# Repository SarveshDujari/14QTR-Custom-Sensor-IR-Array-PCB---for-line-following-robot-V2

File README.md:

# 14-Channel QTR Sensor Array PCB

Custom 14-channel infrared sensor array PCB designed in KiCad for high-speed line follower robots and embedded robotics applications.

---

## Preview

### PCB Layout

### 3D View

---

## Features

- 14× TCRT5000 IR reflectance sensors
- Custom U-shaped curved PCB for wide-angle sensing
- Compact sensor spacing for accurate line detection
- Angled side sensors for better curve and junction detection
- Mounting holes for chassis integration
- Dedicated resistor network for each channel
  - 200Ω IR LED series resistor
  - 10kΩ pull-down resistor
- 16-pin single-row output header
- Analog output for all channels
- Compatible with any ADC-capable microcontroller
- Onboard decoupling capacitor for stable power delivery
- Designed in KiCad 9.0
- Gerber files included for fabrication

---

## Hardware Specifications

| Parameter | Value |
|---|---|
| Sensor Type | TCRT5000 |
| Sensor Count | 14 |
| LED Series Resistor | 200 Ω |
| Pull-down Resistor | 10 kΩ |
| Decoupling Capacitor | 100 nF |
| Supply Voltage | 5V |
| Output Type | Analog |
| Header Type | 16-pin 2.54mm single-row |
| PCB Type | 2-Layer Custom PCB |
| Software Used | KiCad 9.0 |
| Main Application | Line Follower Robotics |

---

## Bill of Materials (BOM)

| Reference | Component | Value | Quantity |
|---|---|---|---|
| U1–U14 | IR Reflectance Sensor | TCRT5000 | 14 |
| R1, R3, R5 ... R27 | LED Series Resistor | 200 Ω (0805) | 14 |
| R2, R4, R6 ... R28 | Pull-down Resistor | 10 kΩ (0805) | 14 |
| C1 | Decoupling Capacitor | 100 nF (0805) | 1 |
| J1 | Pin Header | 16-pin 2.54mm | 1 |
| — | Power Connector | Header / Screw Terminal | 1 |

---

## Pinout

| Pin | Signal | Description |
|---|---|---|
| 1 | GND | Ground |
| 2 | VIN | 5V Supply |
| 3–16 | CH1–CH14 | Analog sensor outputs |

---

## Project Structure

```text
.
├── Gerber new/
├── 14QRT_Custom_IR_Sensor_Improved.kicad_pcb
├── 14QRT_Custom_IR_Sensor_Improved.kicad_pro
├── 14QRT_Custom_IR_Sensor_Improved.kicad_prl
├── fp-info-cache
├── 3d_view.png
├── pcb_editor_view.png
└── README.md
```

---

## Circuit Description

Each channel uses a TCRT5000 infrared reflectance sensor with:

- 200 Ω current-limiting resistor for the IR LED
- 10 kΩ pull-down resistor for the phototransistor output

### IR LED Section

```text
5V ──[200Ω]──► IR LED ──► GND
```

### Phototransistor Section

```text
Collector ──► 5V
Emitter ──► [10kΩ] ──► GND
             │
             └──► Analog Output
```

### Sensor Behavior

| Surface Type | Sensor Output |
|---|---|
| White / Reflective Surface | LOW |
| Black / Non-reflective Surface | HIGH |

---

## Current Status

- PCB routing completed
- Gerber files generated
- Open-source repository published
- Additional improvements planned

---

## Future Improvements

### Hardware

- Add LM393 comparator stage for digital outputs
- Add adjustable threshold potentiometers
- Add onboard I2C ADC for reduced MCU ADC usage
- Add per-channel status LEDs
- Improve power filtering with bulk capacitors
- Add reverse polarity protection

### PCB Layout

- Cleaner routing and optimized power traces
- Better silkscreen labeling
- Dedicated test points for debugging
- Improved sensor wing geometry experiments

### Firmware

- Weighted centroid line position algorithm
- Auto-calibration routine
- PID controller examples for Arduino and STM32

---

## Applications

- High-speed line follower robots
- Autonomous navigation systems
- Embedded robotics platforms
- PID-based motion control systems
- Path tracking robots

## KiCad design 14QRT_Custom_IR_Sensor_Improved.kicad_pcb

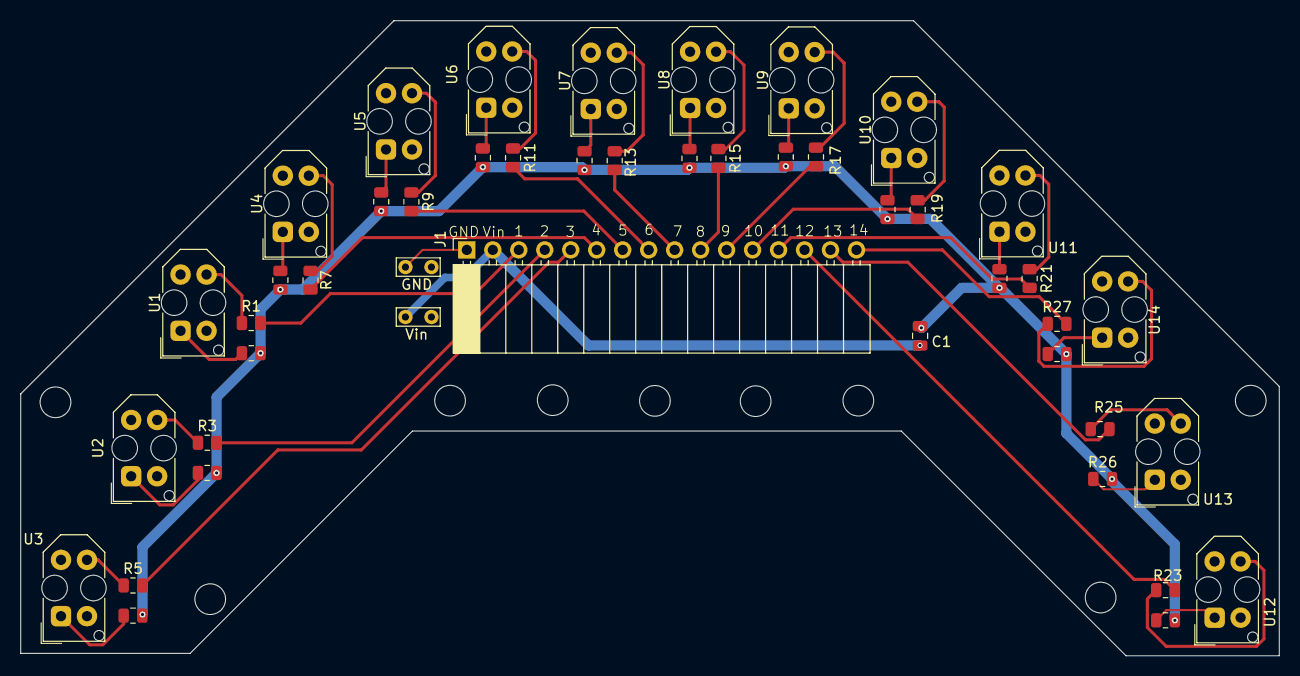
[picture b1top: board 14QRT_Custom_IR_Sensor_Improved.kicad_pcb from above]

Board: 2 copper layers, 123.1 x 62.1 mm, 46 parts (0 on the bottom side), 45 nets.

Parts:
C1: 10uF; C_0805_2012Metric
GND: GND; TestPoint_Bridge_Pitch2.54mm_Drill0.7mm
J1: Conn_01x16_Pin; PinSocket_1x16_P2.54mm_Horizontal
R1, R3, R5, R7, R9, R11, R13, R15, R17, R19, R21, R23, R25, R27: 200; R_0805_2012Metric
R2, R4, R6, R8, R10, R12, R14, R16, R18, R20, R22, R24, R26, R28: 10k; R_0805_2012Metric
U1, U2, U3, U4, U5, U6, U7, U8, U9, U10, U11, U12, U13, U14: TCRT5000; Vishay_TCRT5000
Vin: Vin; TestPoint_Bridge_Pitch2.54mm_Drill0.7mm

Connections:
GND: GND.1, J1.1, U1.2, U1.4, U2.2, U2.4, U3.2, U3.4, U4.2, U4.4, U5.2, U5.4, U6.2, U6.4, U7.2, U7.4, U8.2, U8.4, U9.2, U9.4, U10.2, U10.4, U11.2, U11.4, U12.2, U12.4, U13.2, U13.4, U14.2, U14.4
unnamed: C1.1, R2.2, R4.2, R6.2, R8.2, R10.2, R12.2, R14.2, R16.2, R18.2, R20.2, R22.2, R24.2, R26.2, R28.2
unnamed: C1.2, J1.2, Vin.1
unnamed: R1.1, U1.3
unnamed: R2.1, U1.1
unnamed: R3.1, U2.3
unnamed: R4.1, U2.1
unnamed: R5.1, U3.3
unnamed: R6.1, U3.1
unnamed: R7.1, U4.3
unnamed: R8.1, U4.1
unnamed: R9.1, U5.3
unnamed: R10.1, U5.1
unnamed: R11.1, U6.3
unnamed: R12.1, U6.1
unnamed: R13.1, U7.3
unnamed: R14.1, U7.1
unnamed: R15.1, U8.3
unnamed: R16.1, U8.1
unnamed: R17.1, U9.3
unnamed: R18.1, U9.1
unnamed: R19.1, U10.3
unnamed: R20.1, U10.1
unnamed: R21.1, U11.3
unnamed: R22.1, U11.1
unnamed: R23.1, U12.3
unnamed: R24.1, U12.1
unnamed: R25.1, U13.3
unnamed: R26.1, U13.1
unnamed: R27.1, U14.3
unnamed: R28.1, U14.1
SIG_1: J1.3, R1.2
SIG_2: J1.4, R3.2
SIG_3: J1.5, R5.2
SIG_4: J1.6, R7.2
SIG_5: J1.7, R9.2
SIG_6: J1.8, R11.2
SIG_7: J1.9, R13.2
SIG_8: J1.10, R15.2
SIG_9: J1.11, R17.2
SIG_10: J1.12, R19.2
SIG_11: J1.13, R21.2
SIG_12: J1.14, R23.2
SIG_13: J1.15, R25.2
SIG_14: J1.16, R27.2

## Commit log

2026-05-15 Update README with project details and specifications
2026-05-15 Revise README for clarity and improved layout
    Updated README.md to enhance project details and formatting.
2026-05-15 Update README.md with project details and specifications
